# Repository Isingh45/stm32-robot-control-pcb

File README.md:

# MecaArm Robotic Platform

## Overview

MecaArm is an STM32-based mobile robotic platform developed as the Senior Design Capstone project for **CMPE 492 / CMPE 493** at **California State University, East Bay**.

The platform integrates omnidirectional Mecanum-wheel locomotion, a multi-servo robotic arm, a custom four-layer PCB, embedded firmware, Bluetooth communication, and a mobile application into a complete robotics system.

The project demonstrates end-to-end embedded systems engineering by combining custom hardware design, firmware development, wireless communication, power electronics, and system-level validation.

---

## Technologies

* STM32F429VET6
* ESP32-WROOM-32
* C
* STM32 HAL
* STM32CubeMX
* Bluetooth (UART)
* PWM Motor Control
* Fusion 360 Electronics
* MIT App Inventor
* RT7258 Buck Regulators
* TB6612FNG Motor Drivers

---

## System Architecture

```text
MIT App Inventor Mobile App
             │
        Bluetooth
             │
      ESP32-WROOM-32
             │
      UART (115200 baud)
             │
      STM32F429VET6
      ┌───────────────┐
      │               │
      ▼               ▼
DC Motor Drivers   Servo Control
(TB6612FNG)        (PWM Timers)
      │               │
      ▼               ▼
Mecanum Drive     Robotic Arm
```

---

## Features

* **Custom Four-Layer PCB:** Designed a custom four-layer PCB centered around the STM32F429VET6 microcontroller with dedicated power distribution, motor drivers, communication interfaces, and debugging support.

* **Omnidirectional Mecanum Drive:** Controls four independently driven Mecanum wheels using PWM motor control and dual TB6612FNG motor drivers for omnidirectional robot movement.

* **Robotic Arm Control:** Controls a multi-servo robotic arm using STM32 hardware timers and PWM signals for coordinated actuator movement.

* **Bluetooth Wireless Communication:** Uses an ESP32 as a Bluetooth-to-UART bridge, allowing a custom MIT App Inventor mobile application to wirelessly control the robot.

* **Embedded Firmware:** Developed STM32 firmware using STM32 HAL to manage motor control, servo control, UART communication, and command processing.

* **Multi-Rail Power Architecture:** Designed dedicated power rails for motors, auxiliary peripherals, and logic circuitry to improve electrical stability and isolate high-current motor loads from sensitive electronics.

* **System Integration and Validation:** Successfully demonstrated integrated hardware, firmware, Bluetooth communication, mobile application control, robotic locomotion, and robotic arm operation.

---

## Repository Structure

```text
Documentation/
├── Final Project Report
└── Final Presentation

Hardware/
├── PCB Schematic
├── PCB Layout
├── Fusion 360 Design
├── Bill of Materials
└── Power Budget

Firmware/
├── STM32 Firmware
└── ESP32 Bluetooth Bridge

Mobile-App/
└── MIT App Inventor Application

Validation/
└── System Demonstration Video
```

---

## What I Learned

* Designing custom embedded hardware using a four-layer PCB.
* Developing embedded firmware with STM32 HAL and hardware timers.
* Implementing Bluetooth communication between mobile devices and embedded systems.
* Integrating power electronics, embedded software, wireless communication, and robotic actuators.
* Performing hardware bring-up, debugging, validation, and complete system integration.

---

## Future Improvements

* Add wheel encoder feedback for closed-loop motor control.
* Implement inverse kinematics for robotic arm positioning.
* Integrate ROS 2 for higher-level robot control.
* Add onboard sensors for autonomous navigation.
* Expand the platform with additional perception modules.

---

## Authors

* Inderpal Singh
* Sukhpinder Singh
* Feranmi Falodun
* Pierreline Jacob

**California State University, East Bay**

**CMPE 492 / CMPE 493 – Senior Design Capstone (2025–2026)**

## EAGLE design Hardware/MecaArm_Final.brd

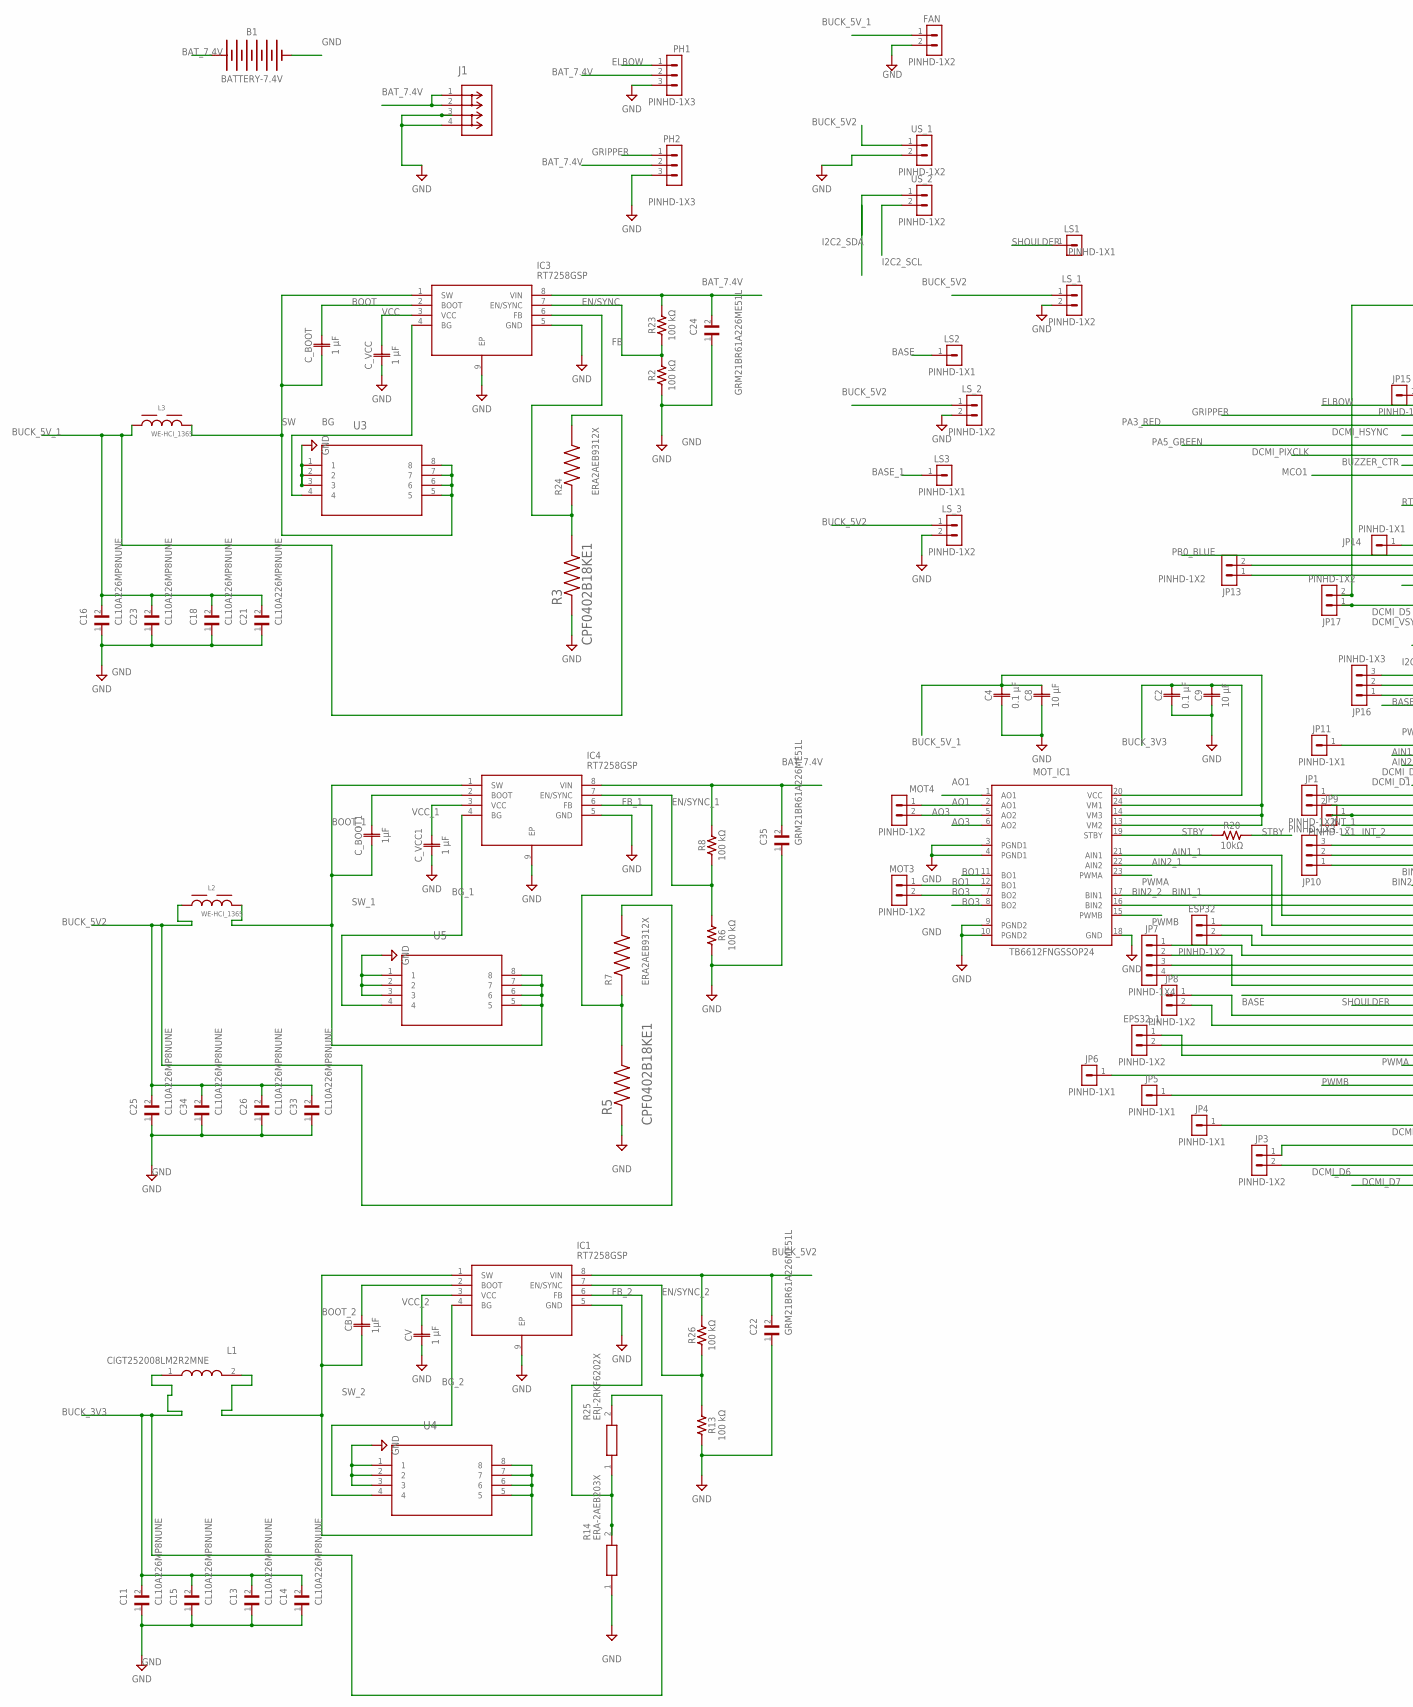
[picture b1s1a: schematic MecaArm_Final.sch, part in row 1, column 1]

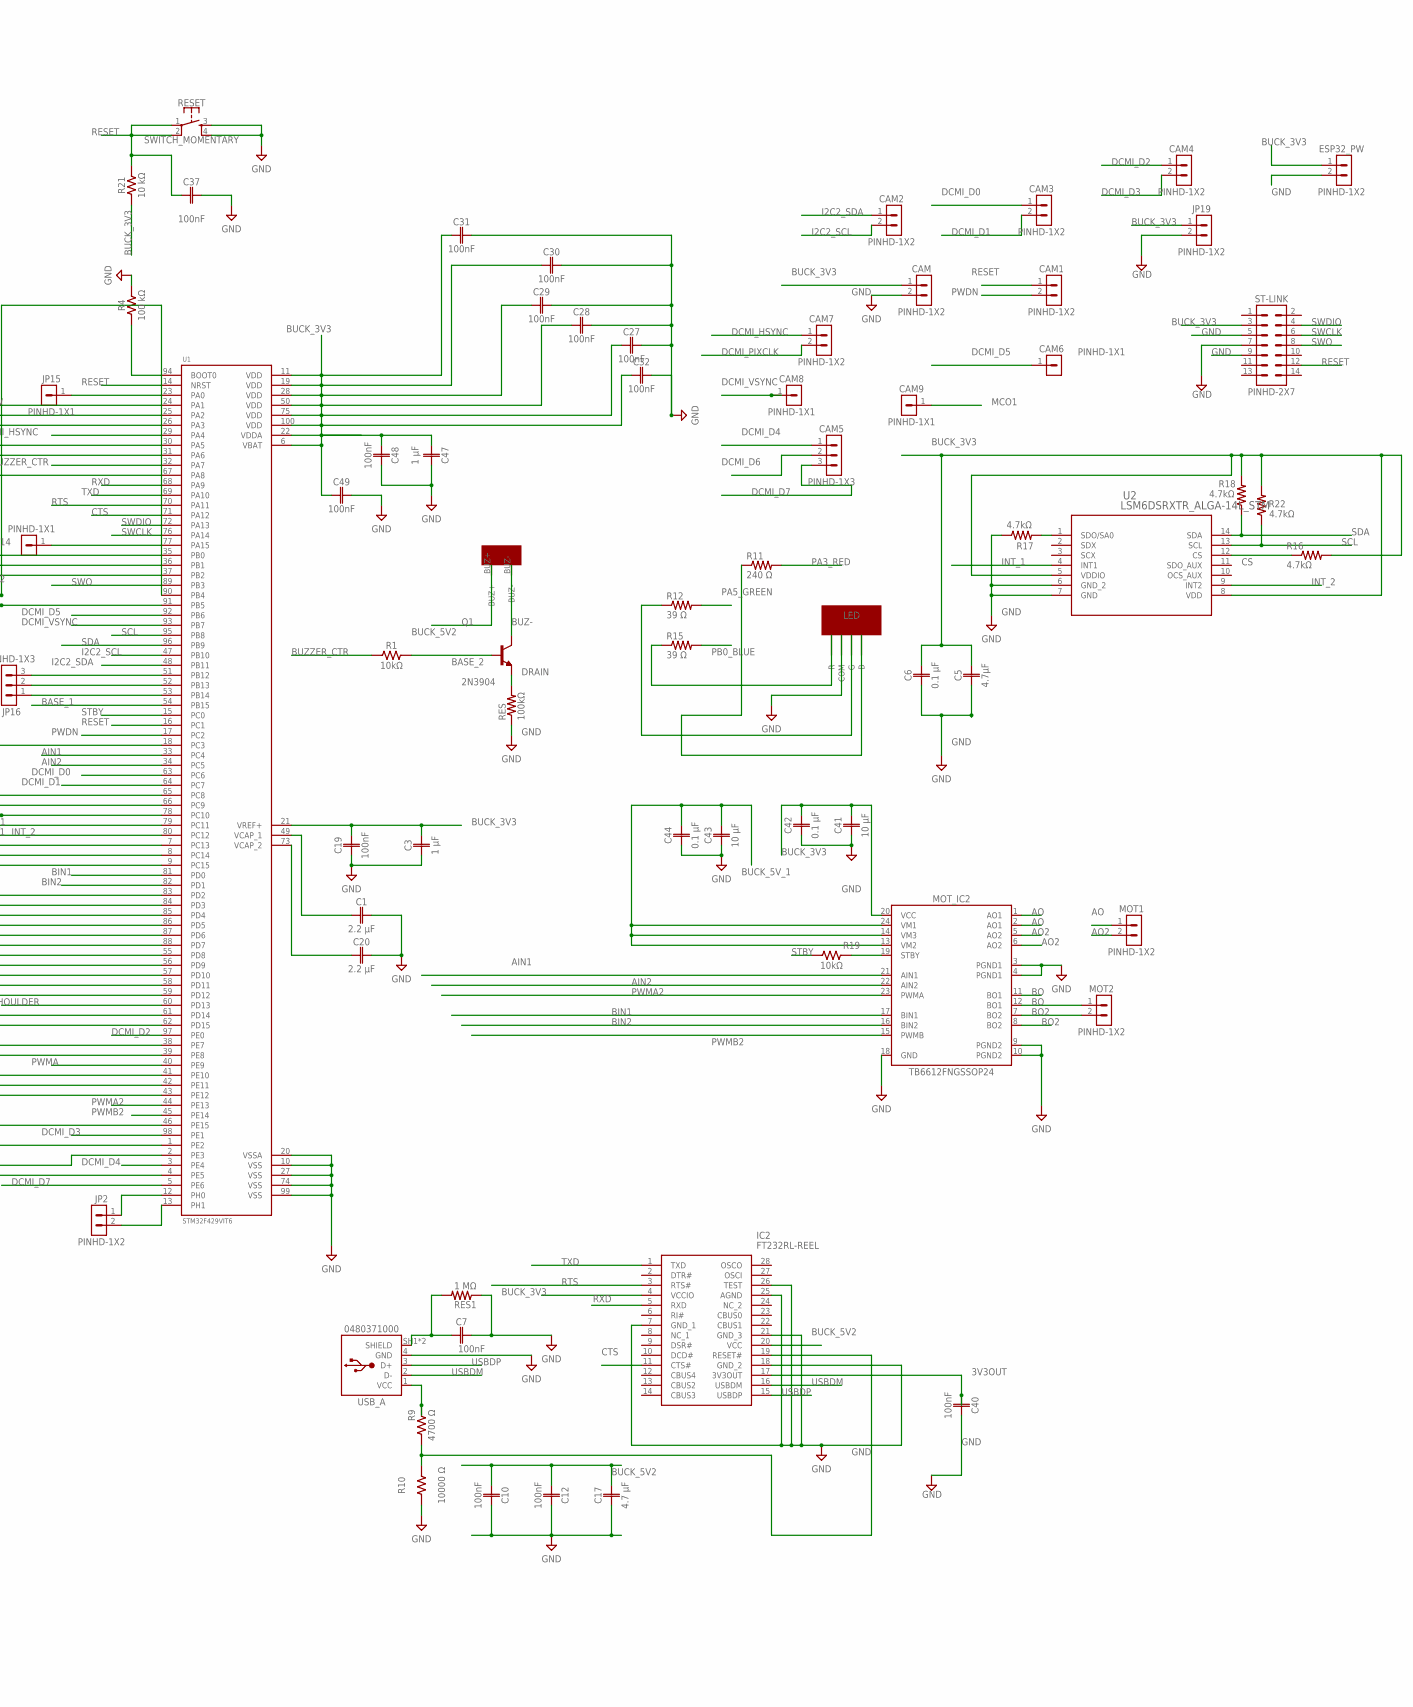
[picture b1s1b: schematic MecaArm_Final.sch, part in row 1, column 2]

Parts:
B1: BATTERY-7.4V; BATTERY-GENERIC
BUZZER: BUZZER_ACTIVE_12X9P5; BUZZER-FOOT
C1, C20: 2.2 µF; CAPC1005X60
C2, C4, C6, C42, C44: 0.1 µF; CAPC1005X60
C3, C47: 1 µF; CAPC1005X60
C5: 4.7µF; CAPC1005X60
C7, C10, C12, C19, C27, C28, C29, C30, C31, C32, C37, C40, C48, C49: 100nF; CAPC1005X60
C8, C9, C41, C43: 10 µF; CAPC1005X60
C11, C13, C14, C15, C16, C18, C21, C23, C25, C26, C33, C34: CL10A226MP8NUNE; CAPC1608X105N
C17: 4.7 μF; CAPC1608X85
C22, C24, C35: GRM21BR61A226ME51L; CAPC2012X140N
CAM, CAM1, CAM2, CAM3, CAM4, CAM7: PINHD-1X2; 1X02
CAM5: PINHD-1X3; 1X03
CAM6, CAM8, CAM9: PINHD-1X1; 1X01
CB: 1µF; CAPC1005X60
CV: 1 µF; CAPC1005X60
C_BOOT: 1 µF; CAPC1005X60
C_BOOT1: 1µF; CAPC1005X60
C_VCC, C_VCC1: 1 µF; CAPC1005X60
EPS32_1: PINHD-1X2; 1X02
ESP32, ESP32_PW: PINHD-1X2; 1X02
FAN: PINHD-1X2; 1X02
IC1, IC3, IC4: RT7258GSP; SOIC127P600X175-9N
IC2: FT232RL-REEL; SOP65P780X200-28N
J1: 1017503CONN_1017491; CONN_1017491
JP1, JP2, JP3, JP8, JP13, JP17, JP19: PINHD-1X2; 1X02
JP4, JP5, JP6, JP9, JP11, JP14, JP15: PINHD-1X1; 1X01
JP7: PINHD-1X4; 1X04
JP10, JP16: PINHD-1X3; 1X03
L1: CIGT252008LM2R2MNE; INDC2520X80N
L2, L3: WE-HCI_1365
LED: LED; LED-FOOT
LS1, LS2, LS3: PINHD-1X1; 1X01
LS_1, LS_2, LS_3: PINHD-1X2; 1X02
MOT1, MOT2, MOT3, MOT4: PINHD-1X2; 1X02
MOT_IC1, MOT_IC2: TB6612FNGSSOP24; SOP65P760X160-24N
PH1, PH2: PINHD-1X3; 1X03
Q1: 2N3904; TO92127P495H495-3
R1: 10kΩ; RESC1005X40
R2, R4, R6, R8, R13, R23, R26: 100 kΩ; RESC1005X40
R3, R5: CPF0402B18KE1; RESC1005X35N
R7, R24: ERA2AEB9312X; RES_ERA2AEB9312X
R9: 4700 Ω; RESC1005X40
R10: 10000 Ω; RESC1005X40
R11: 240 Ω; RESC1005X40
R12, R15: 39 Ω; RESC1005X40
R14: ERA-2AEB203X; ERA2AED122X
R16, R17, R18, R22: 4.7kΩ; RESC1005X40
R19, R20: 10kΩ; RESC2012X65
R21: 10 kΩ; RESC1005X40
R25: ERJ-2RKF6202X; ERJ2RKD1004X
RES: 100kΩ; RESC1005X40
RES1: 1 MΩ; RESC1005X40
RESET: SWITCH_MOMENTARY; SWITCH-MOMENTARY-PTH-6.5MM
ST-LINK: PINHD-2X7; 2X07
U1: STM32F429VIT6; QFP50P1600X1600X160-100N
U2: LSM6DSRXTR_ALGA-14L_STM; LGA-14L_STM
U3, U4, U5: SI7114DN-T1-E3MOSFET_4DN-T1-E3_VIS; MOSFET_4DN-T1-E3_VIS
USB_A: 0480371000
US_1, US_2: PINHD-1X2; 1X02

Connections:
3V3OUT: C40.1, IC2.17 (3V3OUT)
AIN1: MOT_IC2.21 (AIN1), U1.33 (PC4)
AIN1_1: MOT_IC1.21 (AIN1), U1.85 (PD4)
AIN2: MOT_IC2.22 (AIN2), U1.34 (PC5)
AIN2_1: MOT_IC1.22 (AIN2), U1.86 (PD5)
AO: MOT1.1, MOT_IC2.1 (AO1), MOT_IC2.2 (AO1)
AO1: MOT4.1, MOT_IC1.1 (AO1), MOT_IC1.2 (AO1)
AO2: MOT1.2, MOT_IC2.5 (AO2), MOT_IC2.6 (AO2)
AO3: MOT4.2, MOT_IC1.5 (AO2), MOT_IC1.6 (AO2)
BASE: LS2.1, U1.59 (PD12)
BASE_1: LS3.1, U1.54 (PB15)
BASE_2: Q1.2 (B), R1.2
BAT_7.4V: B1.+, C24.2, C35.2, IC3.8 (VIN), IC4.8 (VIN), J1.1, J1.2, PH1.2, PH2.2, R8.2, R23.2
BG: IC3.4 (BG), U3.4
BG_1: IC4.4 (BG), U5.4
BG_2: IC1.4 (BG), U4.4
BIN1: MOT_IC2.17 (BIN1), U1.81 (PD0)
BIN1_1: MOT_IC1.17 (BIN1), U1.83 (PD2)
BIN2: MOT_IC2.16 (BIN2), U1.82 (PD1)
BIN2_2: MOT_IC1.16 (BIN2), U1.84 (PD3)
BO: MOT2.1, MOT_IC2.11 (BO1), MOT_IC2.12 (BO1)
BO1: MOT3.1, MOT_IC1.11 (BO1), MOT_IC1.12 (BO1)
BO2: MOT2.2, MOT_IC2.7 (BO2), MOT_IC2.8 (BO2)
BO3: MOT3.2, MOT_IC1.7 (BO2), MOT_IC1.8 (BO2)
BOOT: C_BOOT.2, IC3.2 (BOOT)
BOOT_1: C_BOOT1.2, IC4.2 (BOOT)
BOOT_2: CB.2, IC1.2 (BOOT)
BUCK_3V3: C2.2, C3.2, C5.2, C6.2, C9.2, C11.2, C13.2, C14.2, C15.2, C19.2, C27.1, C28.1, C29.1, C30.1, C31.1, C32.1, C41.2, C42.2, C49.1, CAM.1, ESP32_PW.1, IC2.4 (VCCIO), JP19.1, L1.1, MOT_IC1.20 (VCC), MOT_IC2.20 (VCC), R16.2, R18.2, R21.1, R22.2, R25.2, ST-LINK.3, U1.6 (VBAT), U1.11 (VDD), U1.19 (VDD), U1.21 (VREF+), U1.28 (VDD), U1.50 (VDD), U1.75 (VDD), U1.100 (VDD), U2.5 (VDDIO), U2.8 (VDD)
BUCK_5V2: BUZZER.BUZ+, C10.1, C12.1, C17.2, C22.2, C25.2, C26.2, C33.2, C34.2, IC1.8 (VIN), IC2.20 (VCC), L2.1, LS_1.1, LS_2.1, LS_3.1, R7.2, R26.2, US_1.1
BUCK_5V_1: C4.2, C8.2, C16.2, C18.2, C21.2, C23.2, C43.2, C44.2, FAN.1, L3.1, MOT_IC1.13 (VM2), MOT_IC1.14 (VM3), MOT_IC1.24 (VM1), MOT_IC2.13 (VM2), MOT_IC2.14 (VM3), MOT_IC2.24 (VM1), R24.2
BUZ-: BUZZER.BUZ-, Q1.3 (C)
BUZZER_CTR: R1.1, U1.32 (PA7)
CS: R16.1, U2.12 (CS)
CTS: IC2.11 (CTS#), U1.71 (PA12)
DCMI_D0: CAM3.1, U1.63 (PC6)
DCMI_D1: CAM3.2, U1.64 (PC7)
DCMI_D2: CAM4.1, U1.97 (PE0)
DCMI_D3: CAM4.2, U1.98 (PE1)
DCMI_D4: CAM5.1, U1.3 (PE4)
DCMI_D5: CAM6.1, U1.92 (PB6)
DCMI_D6: CAM5.2, U1.4 (PE5)
DCMI_D7: CAM5.3, U1.5 (PE6)
DCMI_HSYNC: CAM7.1, U1.29 (PA4)
DCMI_PIXCLK: CAM7.2, U1.31 (PA6)
DCMI_VSYNC: CAM8.1, U1.93 (PB7)
DRAIN: Q1.1 (E), RES.2
ELBOW: PH1.1, U1.24 (PA1)
EN/SYNC: IC3.7 (EN/SYNC), R2.2, R23.1
EN/SYNC_1: IC4.7 (EN/SYNC), R6.2, R8.1
EN/SYNC_2: IC1.7 (EN/SYNC), R13.2, R26.1
FB: IC3.6 (FB), R3.2, R24.1
FB_1: IC4.6 (FB), R5.2, R7.1
FB_2: IC1.6 (FB), R14.2, R25.1
GND: B1.-, C1.2, C2.1, C3.1, C4.1, C5.1, C6.1, C7.2, C8.1, C9.1, C10.2, C11.1, C12.2, C13.1, C14.1, C15.1, C16.1, C17.1, C18.1, C19.1, C20.2, C21.1, C22.1, C23.1, C24.1, C25.1, C26.1, C27.2, C28.2, C29.2, C30.2, C31.2, C32.2, C33.1, C34.1, C35.1, C37.2, C40.2, C41.1, C42.1, C43.1, C44.1, C47.2, C48.2, C49.2, CAM.2, CV.1, C_VCC.1, C_VCC1.1, ESP32_PW.2, FAN.2, IC1.5 (GND), IC1.9 (EP), IC2.7 (GND_1), IC2.18 (GND_2), IC2.21 (GND_3), IC2.25 (AGND), IC2.26 (TEST), IC3.5 (GND), IC3.9 (EP), IC4.5 (GND), IC4.9 (EP), J1.3, J1.4, JP19.2, LED.COM, LS_1.2, LS_2.2, LS_3.2, MOT_IC1.3 (PGND1), MOT_IC1.4 (PGND1), MOT_IC1.9 (PGND2), MOT_IC1.10 (PGND2), MOT_IC1.18 (GND), MOT_IC2.3 (PGND1), MOT_IC2.4 (PGND1), MOT_IC2.9 (PGND2), MOT_IC2.10 (PGND2), MOT_IC2.18 (GND), PH1.3, PH2.3, R2.1, R3.1, R4.2, R5.1, R6.1, R10.1, R13.1, R14.1, R17.1, RES.1, RES1.1, RESET.3, RESET.4, ST-LINK.5, ST-LINK.7, ST-LINK.9, U1.10 (VSS), U1.20 (VSSA), U1.27 (VSS), U1.74 (VSS), U1.99 (VSS), U2.6 (GND_2), U2.7 (GND), U3.1, U3.2, U3.3, U4.1, U4.2, U4.3, U5.1, U5.2, U5.3, USB_A.4 (GND), US_1.2
GRIPPER: PH2.1, U1.25 (PA2)
I2C2_SCL: CAM2.2, U1.47 (PB10), US_2.2
I2C2_SDA: CAM2.1, U1.48 (PB11), US_2.1
INT_1: U1.79 (PC11), U2.4 (INT1)
INT_2: U1.80 (PC12), U2.9 (INT2)
MCO1: CAM9.1, U1.67 (PA8)
unnamed: R4.1, U1.94 (BOOT0)
unnamed: JP2.2, U1.13 (PH1)
unnamed: C20.1, U1.73 (VCAP_2)
unnamed: C47.1, C48.1, U1.22 (VDDA)
unnamed: C1.1, U1.49 (VCAP_1)
unnamed: JP2.1, U1.12 (PH0)
unnamed: JP3.1, U1.1 (PE2)
unnamed: JP3.2, U1.2 (PE3)
unnamed: JP4.1, U1.46 (PE15)
unnamed: JP5.1, U1.43 (PE12)
unnamed: JP6.1, U1.41 (PE10)
unnamed: EPS32_1.2, U1.38 (PE7)
unnamed: EPS32_1.1, U1.39 (PE8)
unnamed: JP8.1, U1.61 (PD14)
unnamed: JP8.2, U1.62 (PD15)
unnamed: ESP32.1, U1.87 (PD6)
unnamed: ESP32.2, U1.88 (PD7)
unnamed: JP7.1, U1.55 (PD8)
unnamed: JP7.3, U1.56 (PD9)
unnamed: JP7.4, U1.57 (PD10)
unnamed: JP7.2, U1.58 (PD11)
unnamed: JP1.1, U1.65 (PC8)
unnamed: JP1.2, U1.66 (PC9)
unnamed: JP9.1, U1.78 (PC10)
unnamed: JP10.3, U1.7 (PC13)
unnamed: JP10.2, U1.8 (PC14)
unnamed: JP10.1, U1.9 (PC15)
unnamed: JP11.1, U1.18 (PC3)
unnamed: JP16.3, U1.51 (PB12)
unnamed: JP16.2, U1.52 (PB13)
unnamed: JP16.1, U1.53 (PB14)
unnamed: JP13.2, U1.36 (PB1)
unnamed: JP13.1, U1.37 (PB2)
unnamed: JP17.2, U1.90 (PB4)
unnamed: R9.2, USB_A.1 (VCC)
unnamed: JP17.1, U1.91 (PB5)
unnamed: JP14.1, U1.77 (PA15)
unnamed: JP15.1, U1.23 (PA0)
PA3_RED: R11.2, U1.26 (PA3)
PA5_GREEN: R12.2, U1.30 (PA5)
PB0_BLUE: R15.2, U1.35 (PB0)
PE13: LED.R, R15.1
PE15: LED.G, R12.1
PE16: LED.B, R11.1
PWDN: CAM1.2, U1.17 (PC2)
PWMA: MOT_IC1.23 (PWMA), U1.40 (PE9)
PWMA2: MOT_IC2.23 (PWMA), U1.44 (PE13)
PWMB: MOT_IC1.15 (PWMB), U1.42 (PE11)
PWMB2: MOT_IC2.15 (PWMB), U1.45 (PE14)
RESET: C37.1, CAM1.1, R21.2, RESET.1, RESET.2, ST-LINK.12, U1.14 (NRST), U1.16 (PC1)
RTS: IC2.3 (RTS#), IC2.19 (RESET#), R9.1, R10.2, U1.70 (PA11)
RXD: IC2.5 (RXD), U1.68 (PA9)
SCL: R22.1, U1.95 (PB8), U2.13 (SCL)
SDA: R18.1, U1.96 (PB9), U2.14 (SDA)
SDO/SA0: R17.2, U2.1 (SDO/SA0)
SHIELD: C7.1, RES1.2, USB_A.SH1 (SHIELD), USB_A.SH2 (SHIELD)
SHOULDER: LS1.1, U1.60 (PD13)
STBY: MOT_IC1.19 (STBY), MOT_IC2.19 (STBY), R19.1, R19.2, R20.1, R20.2, U1.15 (PC0)
SW: C_BOOT.1, IC3.1 (SW), L3.2, U3.5, U3.6, U3.7, U3.8
SWCLK: ST-LINK.6, U1.76 (PA14)
SWDIO: ST-LINK.4, U1.72 (PA13)
SWO: ST-LINK.8, U1.89 (PB3)
SW_1: C_BOOT1.1, IC4.1 (SW), L2.2, U5.5, U5.6, U5.7, U5.8
SW_2: CB.1, IC1.1 (SW), L1.2, U4.5, U4.6, U4.7, U4.8
TXD: IC2.1 (TXD), U1.69 (PA10)
USBDM: IC2.16 (USBDM), USB_A.2 (D-)
USBDP: IC2.15 (USBDP), USB_A.3 (D+)
VCC: C_VCC.2, IC3.3 (VCC)
VCC_1: C_VCC1.2, IC4.3 (VCC)
VCC_2: CV.2, IC1.3 (VCC)

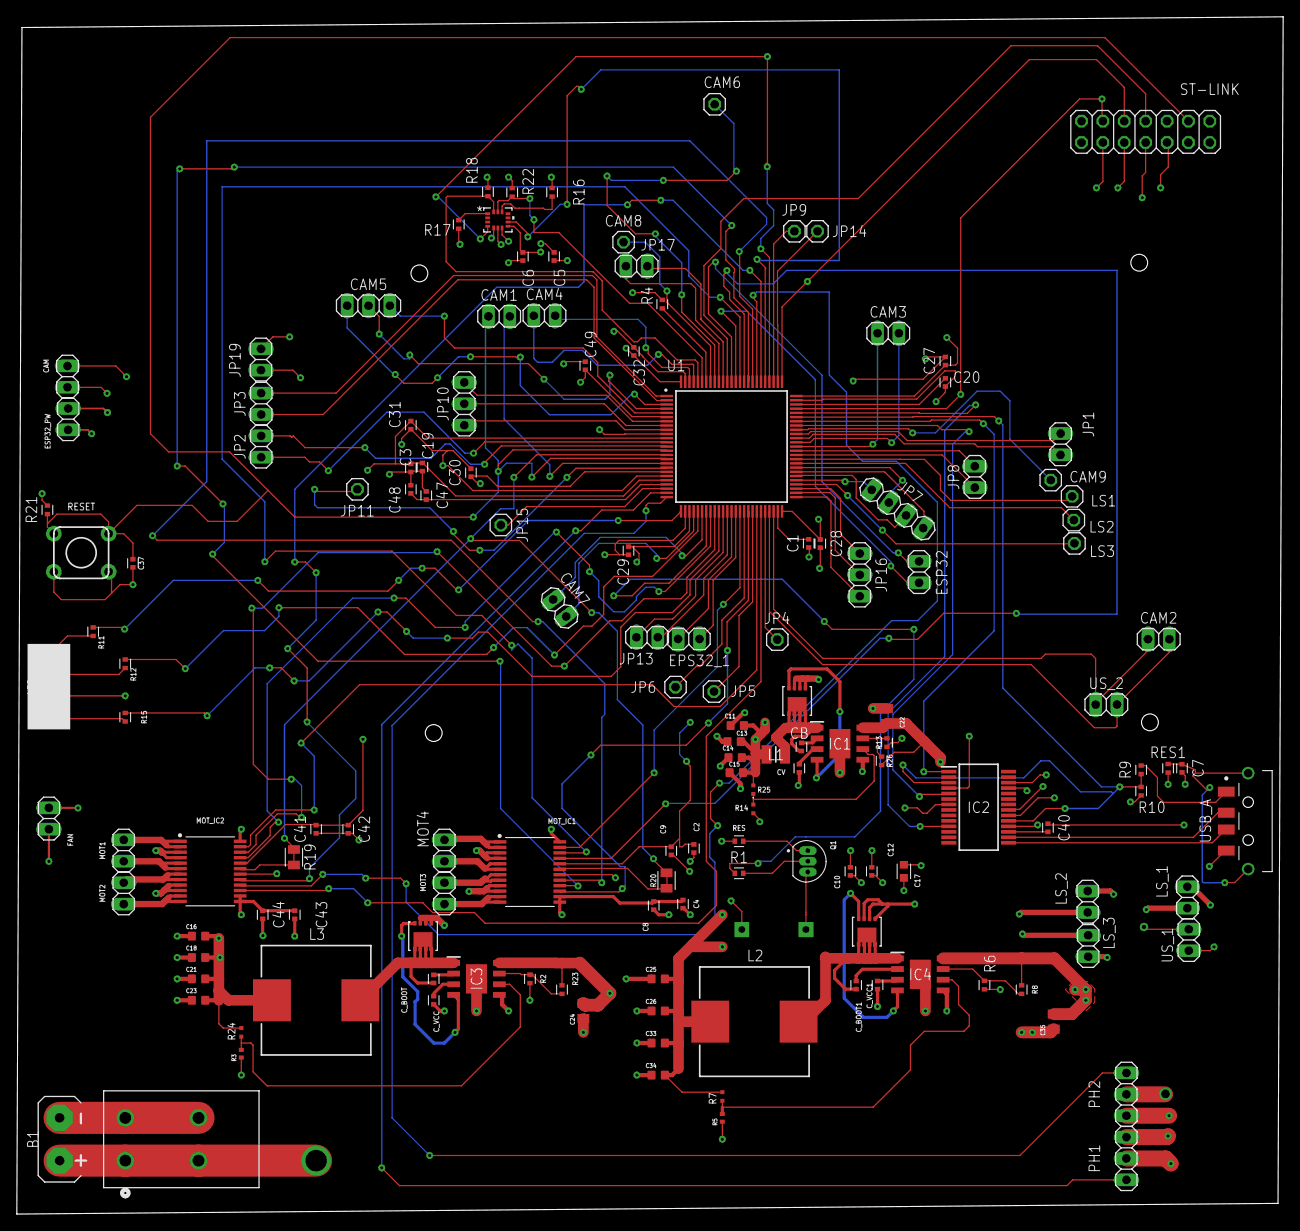
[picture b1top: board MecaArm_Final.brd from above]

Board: 4 copper layers, 150.4 x 142.2 mm, 145 parts (1 on the bottom side), 130 nets.

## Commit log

2025-12-25 Rename schematic.pdf to schematic/schematic.pdf
2025-12-25 top layer
2025-12-25 Rename Screenshot 2025-12-25 131624.png to layout/pcb_top.png
2025-12-25 bottom layer
2025-12-25 Rename Screenshot 2025-12-25 131707.png to layout/pcb_bottom.png
2025-12-25 Rename power_budget.pdf to docs/power_budget.pdf

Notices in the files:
parts and their libraries:
COPYRIGHT: Copyright (C) 2025 Ultra Librarian. All rights reserved.
